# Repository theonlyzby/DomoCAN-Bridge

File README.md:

DomoCAN-Bridge
==============

Replace your EZL-50 card by a Raspberry Pi and some extra HW

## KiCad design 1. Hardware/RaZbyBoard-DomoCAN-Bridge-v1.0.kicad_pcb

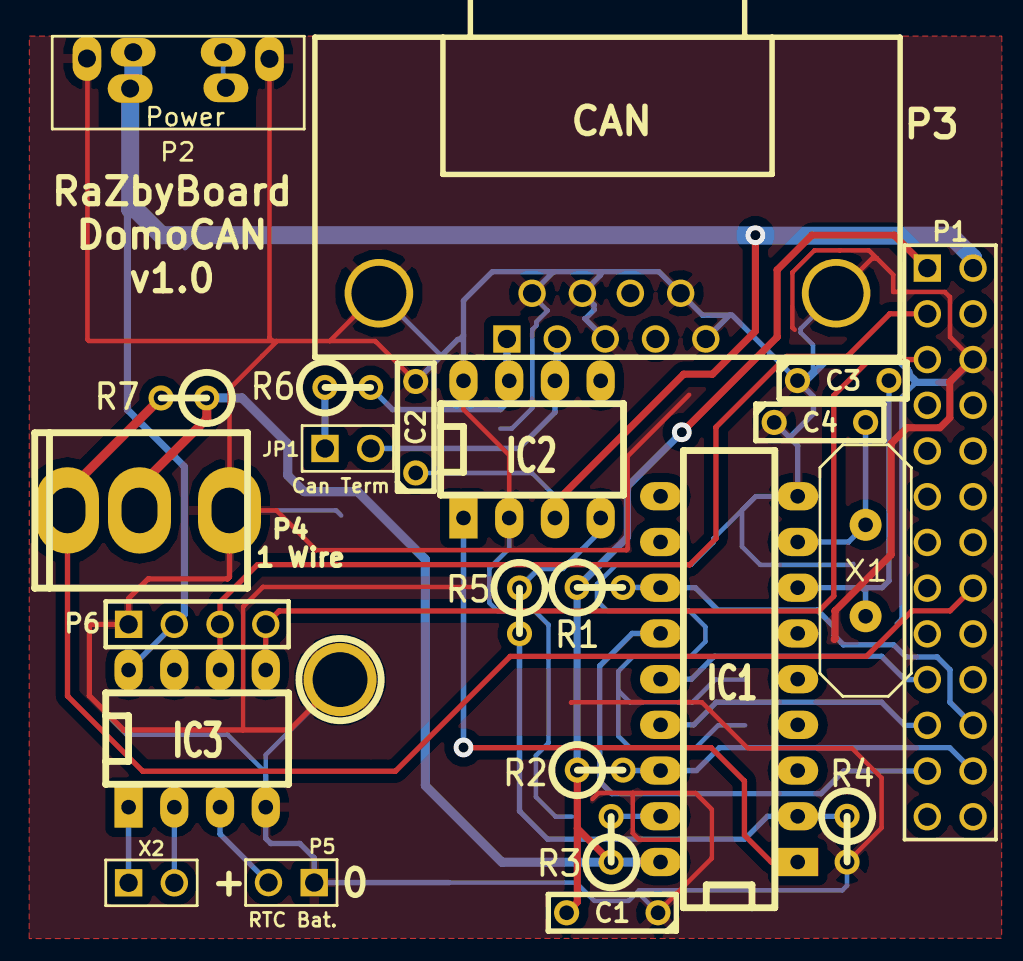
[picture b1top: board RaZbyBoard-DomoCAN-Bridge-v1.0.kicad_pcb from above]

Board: 2 copper layers, 24 parts (0 on the bottom side), 24 nets.

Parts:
C1, C2: 100nF; C2
C3, C4: 22pF; C2
IC1: MCP2515; DIP-18__300_ELL
IC2: MCP2551; DIP-8__300_ELL
IC3: DS1307; DIP-8__300_ELL
JP1: Can Term; PIN_ARRAY_2X1
P1: Raspberry Pi; pin_array_13x2
P2: Power; miniDIN4-2Print
P3: CAN; DB9FC
P4: 1 Wire; JACK_3.5mm_Stereo_2Print
P5: RTC Bat.; PIN_ARRAY_2X1
P6: CONN_4; PIN_ARRAY_4x1
P999: CONN_1; 1pin
R1, R2, R3: 6.8K; R1
R4: 18K; R1
R5: 10K; R1
R6: 120; R1
R7: 4.7K; R1
X1: 16MHz; HC-18UV
X2: 32.768KHz; PIN_ARRAY_2X1

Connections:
3.3 V: C1.2, IC1.18, P1.1, P4.3, R1.1, R2.1, R3.1, R7.1
5.0 V: C2.1, IC2.3, IC3.8, P1.2, P2.2, P2.3, P6.2
12 V: P2.1, P2.4
GND: C1.1, C2.2, C3.1, C4.1, IC1.9, IC2.2, IC2.8, IC3.4, P1.6, P2.5, P2.6, P3.3, P3.5, P3.6, P3.7, P3.9, P4.1, P5.1, P6.1, P999.1, R4.2
GPIO 4: P1.16, P4.2, R7.2
GPIO 6: IC1.12, P1.22, R1.2
I2C_SCL: IC3.5, P1.5, P6.4
I2C_SDA: IC3.6, P1.3, P6.3
unnamed: IC1.17, R3.2
unnamed: IC2.6, JP1.2, P3.2
unnamed: IC2.7, P3.1, R6.2
unnamed: IC1.2, R4.1, R5.2
unnamed: JP1.1, R6.1
unnamed: IC1.1, IC2.1
unnamed: IC3.3, P5.2
unnamed: IC3.2, X2.2
unnamed: IC3.1, X2.1
unnamed: IC2.4, R5.1
unnamed: C4.2, IC1.8, X1.2
unnamed: C3.2, IC1.7, X1.1
SPI_CE0: IC1.16, P1.24, R2.2
SPI_MISO: IC1.15, P1.21
SPI_MOSI: IC1.14, P1.19
SPI_SCLK: IC1.13, P1.23

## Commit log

2013-06-13 v1.0
